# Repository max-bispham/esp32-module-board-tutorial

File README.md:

# esp32-module-board-tutorial
Tutorial design I followed in order to learn kicad, pcb design process and schematic layout

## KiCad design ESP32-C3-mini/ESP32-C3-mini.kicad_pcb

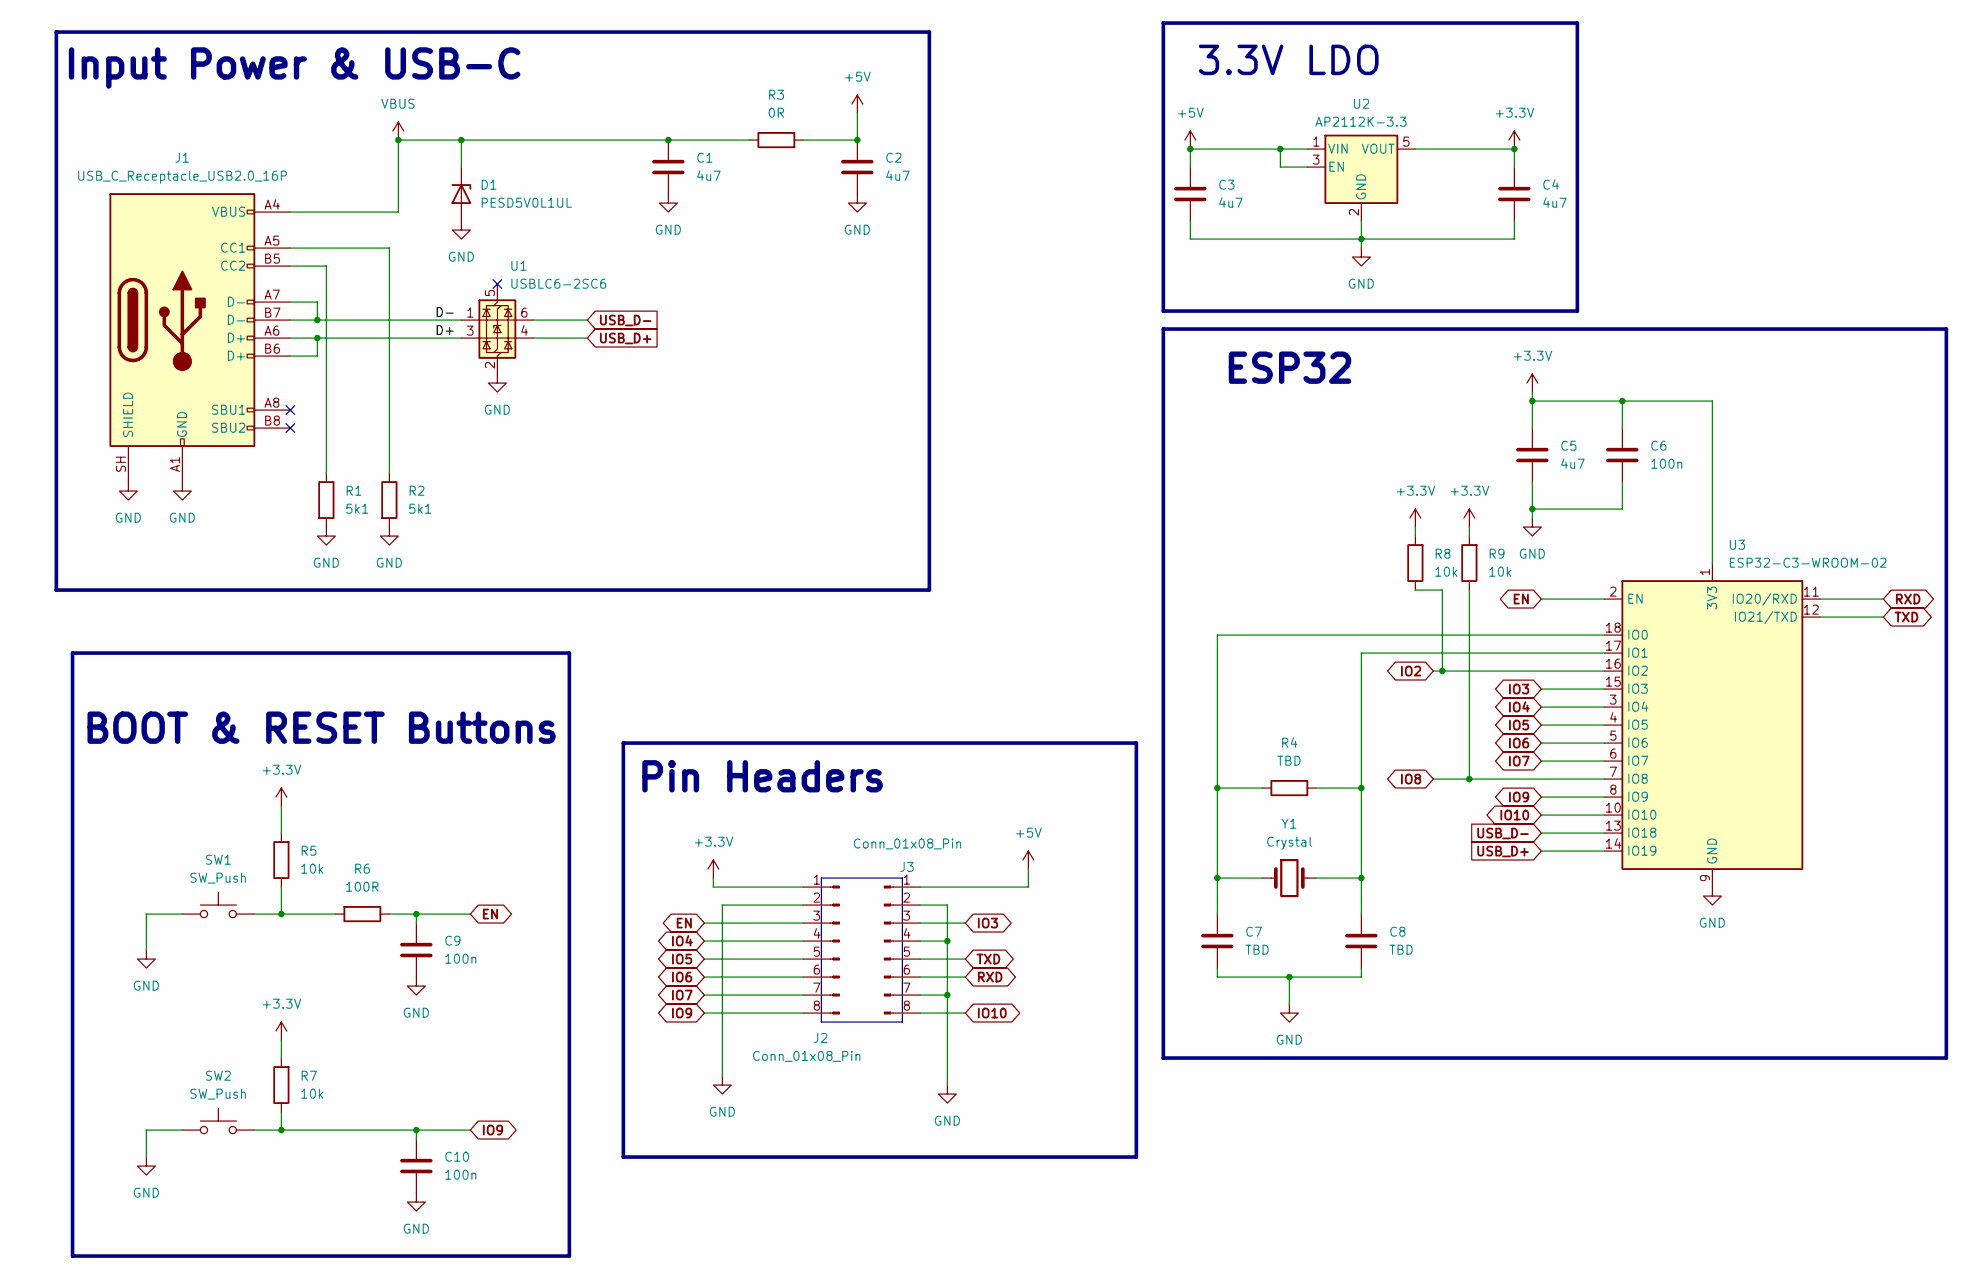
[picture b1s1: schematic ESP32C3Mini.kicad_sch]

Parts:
C1, C2, C3, C4, C5: 4u7; C_0805_2012Metric
C6, C9, C10: 100n; C_0402_1005Metric
C7, C8: TBD; C_0201_0603Metric
D1: PESD5V0L1UL; D_SOD-882
J1: USB_C_Receptacle_USB2.0_16P; USB_C_Receptacle_G-Switch_GT-USB-7010ASV
J2, J3: Conn_01x08_Pin; PinHeader_1x08_P2.54mm_Vertical
R1, R2: 5k1; R_0402_1005Metric
R3: 0R; R_0805_2012Metric
R4: TBD; R_0201_0603Metric
R5, R7, R8, R9: 10k; R_0201_0603Metric
R6: 100R; R_0201_0603Metric
SW1, SW2: SW_Push; SW_SPST_B3U-1000P
U1: USBLC6-2SC6; SOT-23-6
U2: AP2112K-3.3; SOT-23-5
U3: ESP32-C3-WROOM-02
Y1: Crystal; Crystal_SMD_3215-2Pin_3.2x1.5mm

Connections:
+3.3V: C4.1, C5.2, C6.1, J2.1, R5.2, R7.2, R8.2, R9.2, U2.5 (VOUT), U3.1 (3V3)
+5V: C2.1, C3.1, J3.1, R3.2, U2.1 (VIN), U2.3 (EN)
/ESP32-C3-Mini/D+: J1.A6 (D+), J1.B6 (D+), U1.3 (I/O2)
/ESP32-C3-Mini/D-: J1.A7 (D-), J1.B7 (D-), U1.1 (I/O1)
EN: C9.1, J2.3, R6.1, U3.2 (EN)
GND: C1.2, C2.2, C3.2, C4.2, C5.1, C6.2, C7.2, C8.2, C9.2, C10.2, D1.2 (A), J1.A1 (GND), J1.A12 (GND), J1.B1 (GND), J1.B12 (GND), J1.SH (SHIELD), J2.2, J3.2, J3.4, J3.7, R1.2, R2.2, SW1.1, SW2.1, U1.2 (GND), U2.2 (GND), U3.9 (GND), U3.19 (GND)
IO2: R8.1, U3.16 (IO2)
IO3: J3.3, U3.15 (IO3)
IO4: J2.4, U3.3 (IO4)
IO5: J2.5, U3.4 (IO5)
IO6: J2.6, U3.5 (IO6)
IO7: J2.7, U3.6 (IO7)
IO8: R9.1, U3.7 (IO8)
IO9: C10.1, J2.8, R7.1, SW2.2, U3.8 (IO9)
IO10: J3.8, U3.10 (IO10)
unnamed: J1.A5 (CC1), R2.1
unnamed: J1.B5 (CC2), R1.1
unnamed: R5.1, R6.2, SW1.2
unnamed: C7.1, R4.1, U3.18 (IO0), Y1.1
unnamed: C8.1, R4.2, U3.17 (IO1), Y1.2
RXD: J3.6, U3.11 (IO20/RXD)
TXD: J3.5, U3.12 (IO21/TXD)
USB_D+: U1.4 (I/O2), U3.14 (IO19)
USB_D-: U1.6 (I/O1), U3.13 (IO18)
VBUS: C1.1, D1.1 (K), J1.A4 (VBUS), J1.A9 (VBUS), J1.B4 (VBUS), J1.B9 (VBUS), R3.1

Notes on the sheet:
Pin Headers
ESP32
Input Power & USB-C
BOOT & RESET Buttons
3.3V LDO

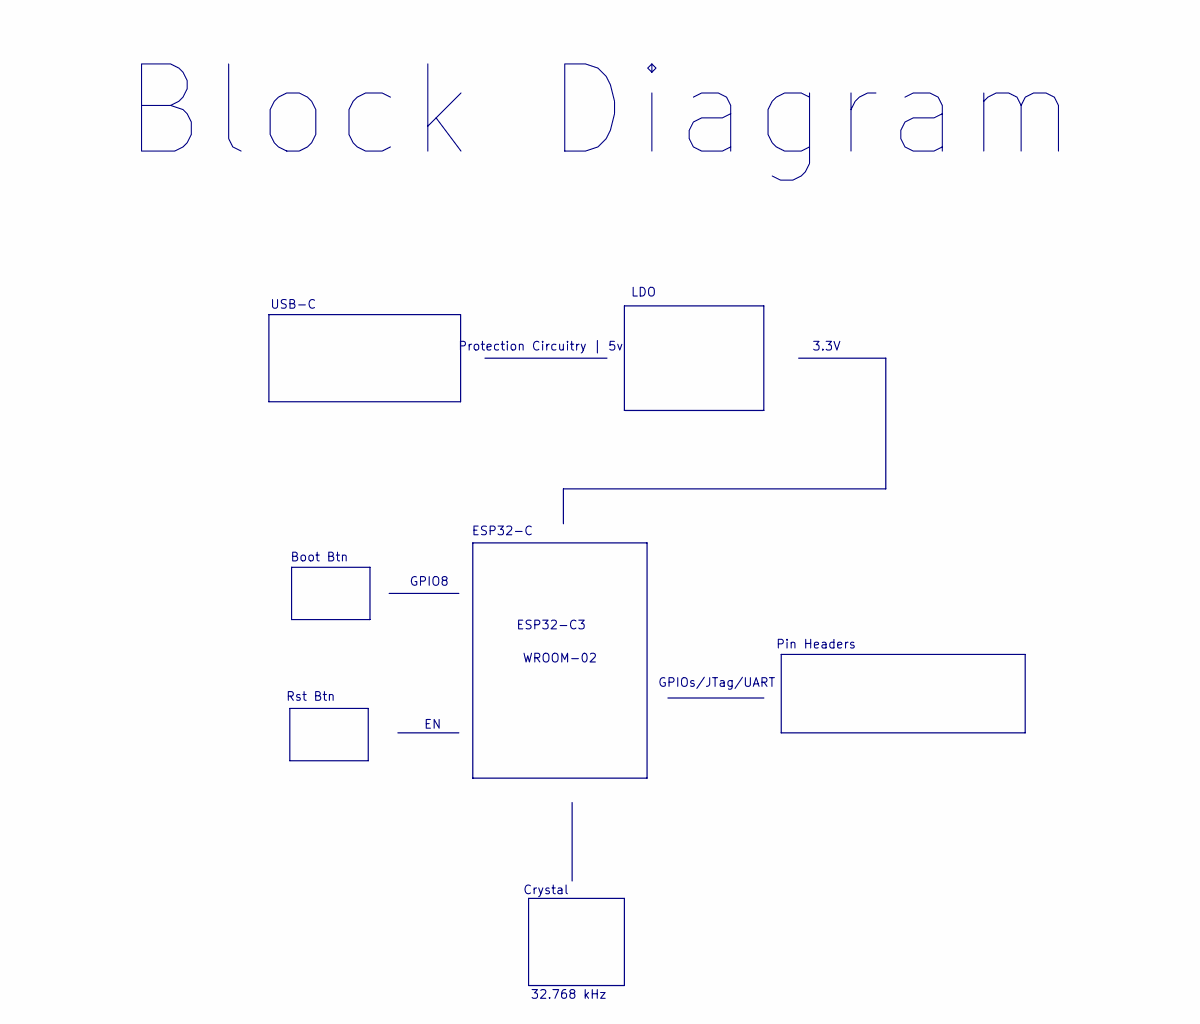
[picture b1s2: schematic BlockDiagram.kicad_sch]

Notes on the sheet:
3.3V
Rst Btn
GPIOs/JTag/UART
ESP32-C3
USB-C
Protection Circuitry | 5v
WROOM-02
GPIO8
32.768 kHz
Pin Headers
Block Diagram
LDO
Boot Btn
ESP32-C
Crystal

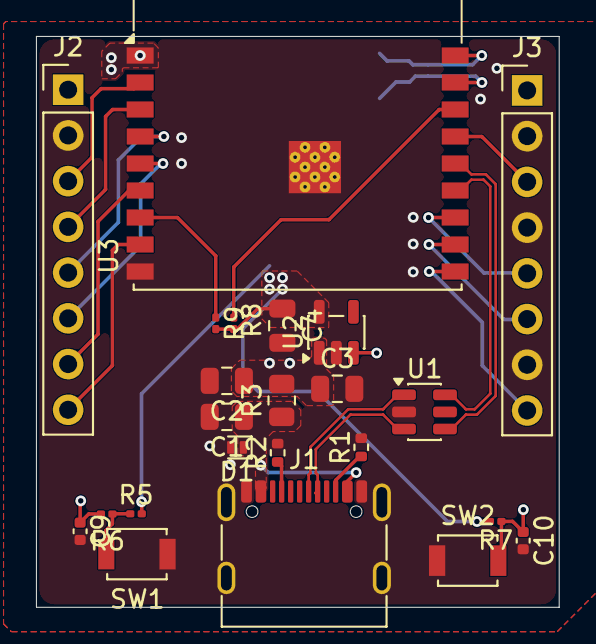
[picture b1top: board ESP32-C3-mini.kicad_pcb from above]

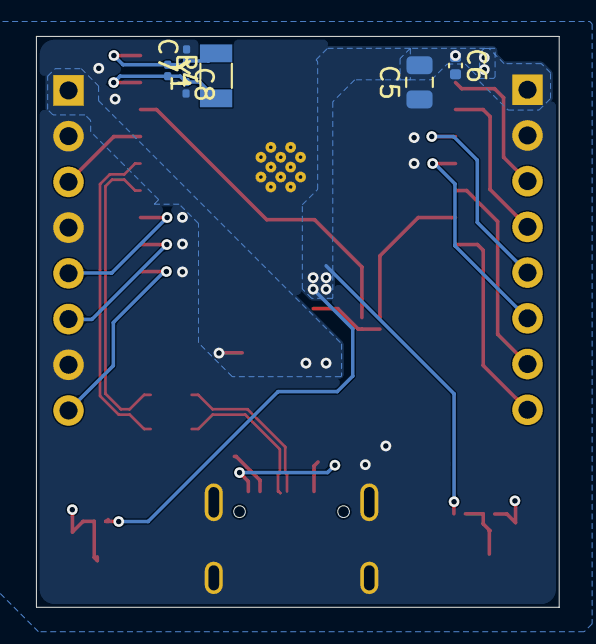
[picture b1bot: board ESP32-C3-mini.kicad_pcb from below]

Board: 4 copper layers, 29.0 x 31.7 mm, 29 parts (6 on the bottom side), 25 nets.
